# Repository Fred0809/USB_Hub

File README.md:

# USB_Hub

This is a project on USB hub/switch. Two input devices, toggle switch, and up to 4 output devices

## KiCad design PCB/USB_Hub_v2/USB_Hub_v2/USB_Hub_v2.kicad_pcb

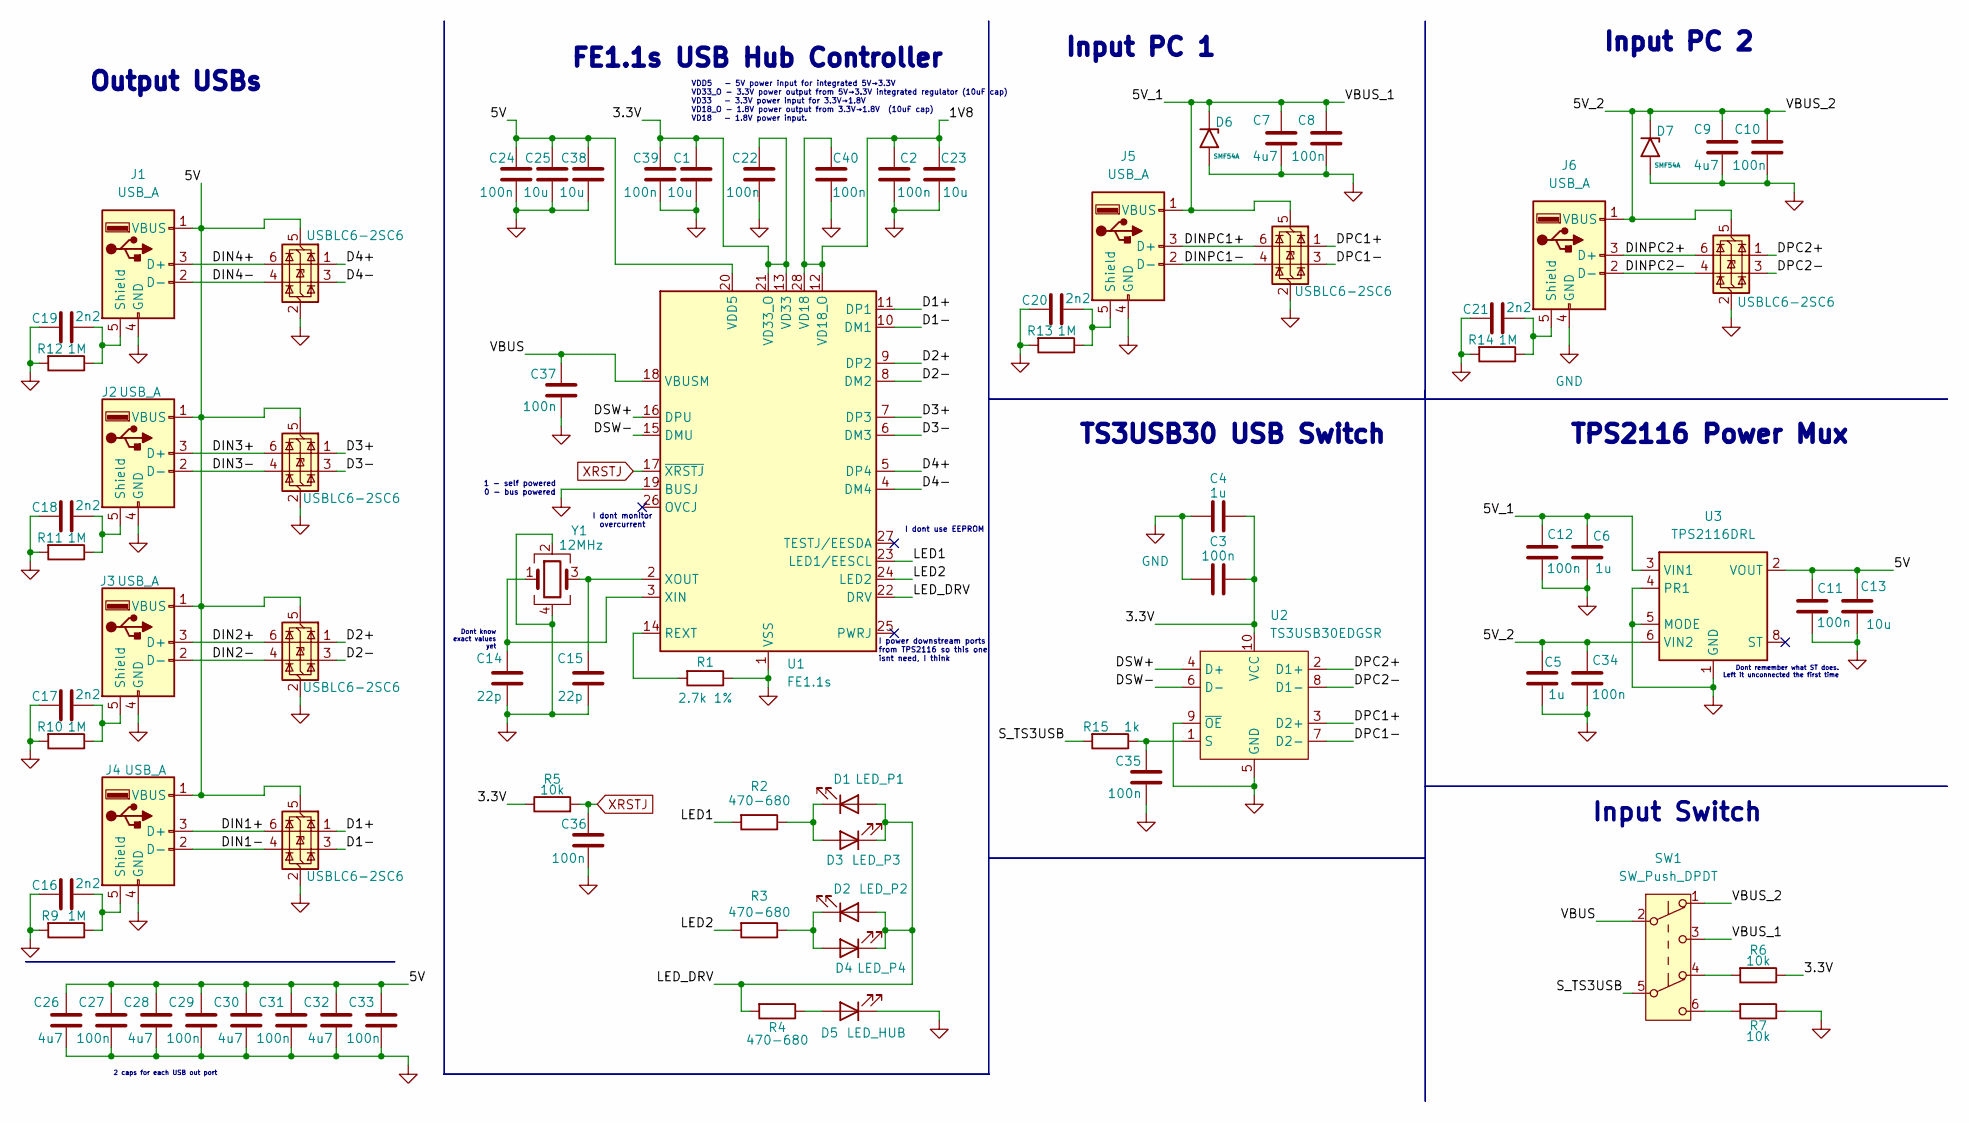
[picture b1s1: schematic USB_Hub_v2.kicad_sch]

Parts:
C1, C13, C23, C25, C38: 10u; C_0805_2012Metric_Pad1.18x1.45mm_HandSolder
C2, C3, C8, C10, C11, C12, C22, C24, C27, C29, C31, C33, C34, C35, C36, C37, C39, C40: 100n; C_0805_2012Metric_Pad1.18x1.45mm_HandSolder
C4, C5, C6: 1u; C_0805_2012Metric_Pad1.18x1.45mm_HandSolder
C7, C9, C26, C28, C30, C32: 4u7; C_0805_2012Metric_Pad1.18x1.45mm_HandSolder
C14, C15: 22p; C_0805_2012Metric_Pad1.18x1.45mm_HandSolder
C16, C17, C18, C19, C20, C21: 2n2; C_0805_2012Metric_Pad1.18x1.45mm_HandSolder
D1: LED_P1; LED_0805_2012Metric_Pad1.15x1.40mm_HandSolder
D2: LED_P2; LED_0805_2012Metric_Pad1.15x1.40mm_HandSolder
D3: LED_P3; LED_0805_2012Metric_Pad1.15x1.40mm_HandSolder
D4: LED_P4; LED_0805_2012Metric_Pad1.15x1.40mm_HandSolder
D5: LED_HUB; LED_0805_2012Metric_Pad1.15x1.40mm_HandSolder
D6, D7: SMF54A; D_SMF
J1, J2, J3, J4, J5, J6: USB_A; USB_A_Molex_67643_Horizontal
R1: 2.7k 1%; R_0603_1608Metric_Pad0.98x0.95mm_HandSolder
R2, R3, R4: 470-680; R_0603_1608Metric_Pad0.98x0.95mm_HandSolder
R5, R6, R7: 10k; R_0603_1608Metric_Pad0.98x0.95mm_HandSolder
R9, R10, R11, R12, R13, R14: 1M; R_0603_1608Metric_Pad0.98x0.95mm_HandSolder
R15: 1k; R_0603_1608Metric_Pad0.98x0.95mm_HandSolder
SW1: SW_Push_DPDT; SW_NKK_G1xJP
U1: FE1.1s; SSOP-28_3.9x9.9mm_P0.635mm
U2: TS3USB30EDGSR; VSSOP-10_3x3mm_P0.5mm
U3: TPS2116DRL; SOT-583-8
U4, U5, U6, U7, U8, U9: USBLC6-2SC6; SOT-23-6
Y1: 12MHz; Crystal_SMD_3225-4Pin_3.2x2.5mm

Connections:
/1V8: C2.2, C23.2, C40.2, U1.12 (VD18_O), U1.28 (VD18)
/3.3V: C1.2, C3.2, C4.2, C22.2, C39.2, R5.1, R6.1, U1.13 (VD33), U1.21 (VD33_O), U2.10 (VCC)
/5V: C11.1, C13.2, C24.2, C25.2, C26.2, C27.2, C28.2, C29.2, C30.2, C31.2, C32.2, C33.2, C38.2, J1.1 (VBUS), J2.1 (VBUS), J3.1 (VBUS), J4.1 (VBUS), U1.20 (VDD5), U3.2 (VOUT), U3.7 (VOUT), U4.5 (VBUS), U5.5 (VBUS), U6.5 (VBUS), U7.5 (VBUS)
/5V_1: C6.2, C7.2, C8.2, C12.1, D6.1 (A1), J5.1 (VBUS), SW1.3 (C), U3.3 (VIN1), U8.5 (VBUS)
/5V_2: C5.2, C9.2, C10.2, C34.1, D7.1 (A1), J6.1 (VBUS), SW1.1 (A), U3.6 (VIN2), U9.5 (VBUS)
/D1+: U1.11 (DP1), U7.1 (I/O1)
/D1-: U1.10 (DM1), U7.3 (I/O2)
/D2+: U1.9 (DP2), U6.1 (I/O1)
/D2-: U1.8 (DM2), U6.3 (I/O2)
/D3+: U1.7 (DP3), U5.1 (I/O1)
/D3-: U1.6 (DM3), U5.3 (I/O2)
/D4+: U1.5 (DP4), U4.1 (I/O1)
/D4-: U1.4 (DM4), U4.3 (I/O2)
/DIN1+: J4.3 (D+), U7.6 (I/O1)
/DIN1-: J4.2 (D-), U7.4 (I/O2)
/DIN2+: J3.3 (D+), U6.6 (I/O1)
/DIN2-: J3.2 (D-), U6.4 (I/O2)
/DIN3+: J2.3 (D+), U5.6 (I/O1)
/DIN3-: J2.2 (D-), U5.4 (I/O2)
/DIN4+: J1.3 (D+), U4.6 (I/O1)
/DIN4-: J1.2 (D-), U4.4 (I/O2)
/DINPC1+: J5.3 (D+), U8.6 (I/O1)
/DINPC1-: J5.2 (D-), U8.4 (I/O2)
/DINPC2+: J6.3 (D+), U9.6 (I/O1)
/DINPC2-: J6.2 (D-), U9.4 (I/O2)
/DPC1+: U2.3 (D2+), U8.1 (I/O1)
/DPC1-: U2.7 (D2-), U8.3 (I/O2)
/DPC2+: U2.2 (D1+), U9.1 (I/O1)
/DPC2-: U2.8 (D1-), U9.3 (I/O2)
/DSW+: U1.16 (DPU), U2.4 (D+)
/DSW-: U1.15 (DMU), U2.6 (D-)
/LED1: R2.2, U1.23 (LED1/EESCL)
/LED2: R3.2, U1.24 (LED2)
/LED_DRV: D1.2 (A), D2.2 (A), D3.1 (K), D4.1 (K), R4.2, U1.22 (DRV)
/S_TS3USB: R15.2, SW1.5 (B)
/VBUS: C37.2, SW1.2 (B), U1.18 (VBUSM)
GND: C1.1, C2.1, C3.1, C4.1, C5.1, C6.1, C7.1, C8.1, C9.1, C10.1, C11.2, C12.2, C13.1, C14.1, C15.1, C16.1, C17.1, C18.1, C19.1, C20.1, C21.1, C22.1, C23.1, C24.1, C25.1, C26.1, C27.1, C28.1, C29.1, C30.1, C31.1, C32.1, C33.1, C34.2, C35.1, C36.1, C37.1, C38.1, C39.1, C40.1, D5.1 (K), D6.2 (A2), D7.2 (A2), J1.4 (GND), J2.4 (GND), J3.4 (GND), J4.4 (GND), J5.4 (GND), J6.4 (GND), R1.1, R7.1, R9.2, R10.2, R11.2, R12.2, R13.2, R14.2, U1.1 (VSS), U1.19 (BUSJ), U2.5 (GND), U2.9 (~OE), U3.1 (GND), U3.4 (PR1), U3.5 (MODE), U4.2 (GND), U5.2 (GND), U6.2 (GND), U7.2 (GND), U8.2 (GND), U9.2 (GND), Y1.2, Y1.4
unnamed: D1.1 (K), D3.2 (A), R2.1
unnamed: D2.1 (K), D4.2 (A), R3.1
unnamed: D5.2 (A), R4.1
unnamed: C19.2, J1.5 (Shield), R12.1
unnamed: C18.2, J2.5 (Shield), R11.1
unnamed: C17.2, J3.5 (Shield), R10.1
unnamed: C16.2, J4.5 (Shield), R9.1
unnamed: C20.2, J5.5 (Shield), R13.1
unnamed: C21.2, J6.5 (Shield), R14.1
unnamed: R6.2, SW1.4 (A)
unnamed: R7.2, SW1.6 (C)
unnamed: R1.2, U1.14 (REXT)
unnamed: C14.2, U1.3 (XIN), Y1.1
unnamed: C15.2, U1.2 (XOUT), Y1.3
unnamed: C35.2, R15.1, U2.1 (S)
XRSTJ: C36.2, R5.2, U1.17 (~XRSTJ)

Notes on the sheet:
Input PC 2
TS3USB30 USB Switch
I dont use EEPROM
TPS2116 Power Mux
Input PC 1
FE1.1s USB Hub Controller
Output USBs
VDD5 - 5V power input for integrated 5V→3.3V VD33_O - 3.3V power output from 5V→3.3V integrated regulator (10uF cap) VD33 - 3.3V power input for 3.3V→1.8V VD18_O - 1.8V power output from 3.3V→1.8V (10uF cap) VD18 - 1.8V power input.
Dont remember what ST does. Left it unconnected the first time
1 - self powered 0 - bus powered
2 caps for each USB out port
Input Switch
Dont know exact values yet
I dont monitor overcurrent
I power downstream ports from TPS2116 so this one isnt need, I think

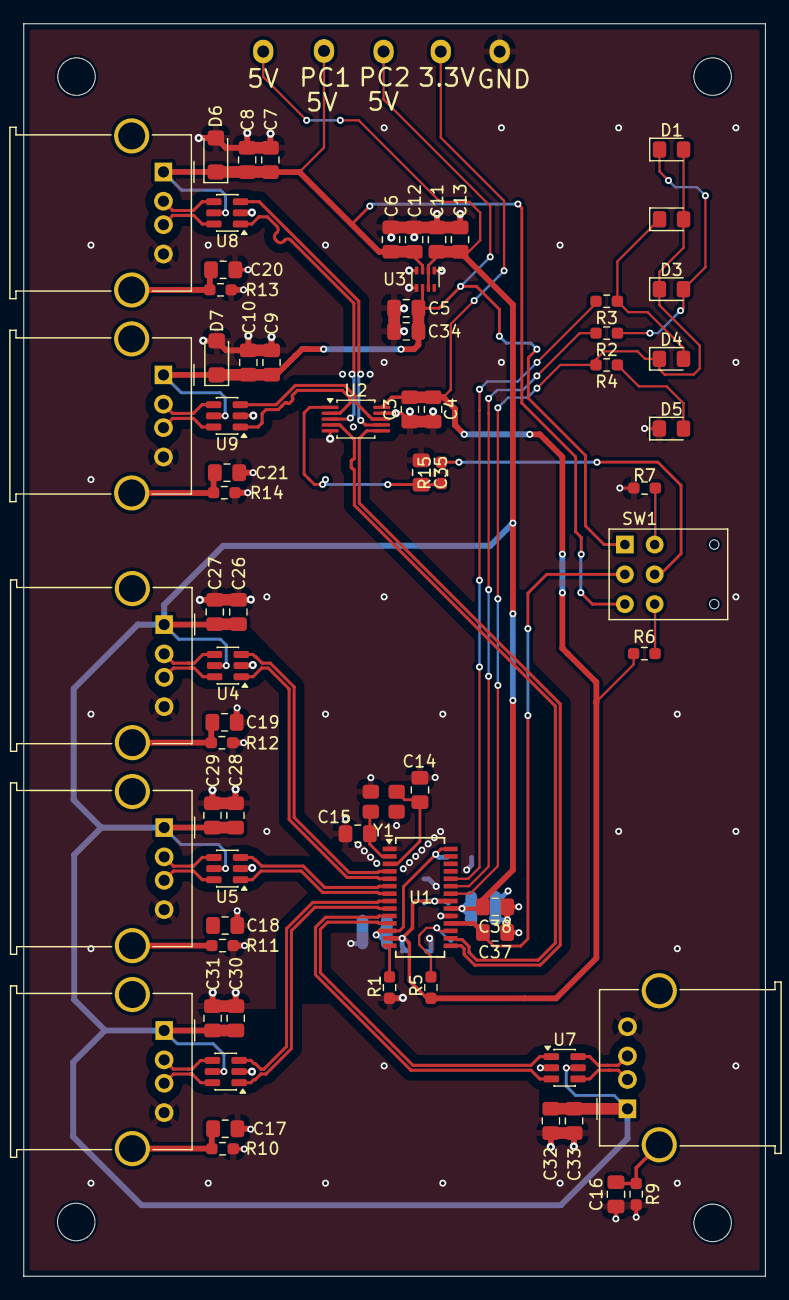
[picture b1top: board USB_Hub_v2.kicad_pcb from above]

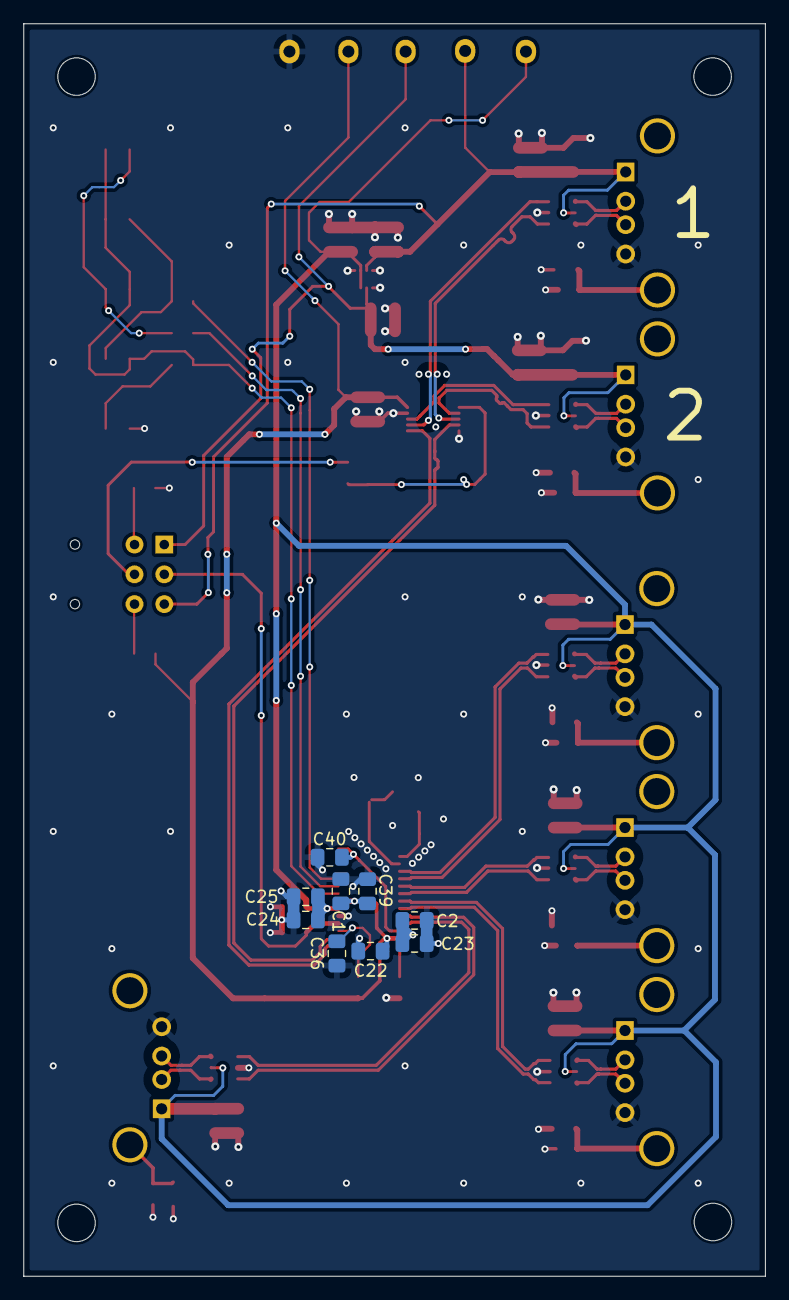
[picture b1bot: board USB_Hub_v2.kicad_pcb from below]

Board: 4 copper layers, 63.2 x 106.8 mm, 78 parts (9 on the bottom side), 53 nets.

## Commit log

2025-12-28 Add PCB images and USB hub schematic
    Added PCB_1.png and PCB_2.png images along with USB_Hub.pdf schematic to the PCB directory for documentation and reference.
2025-12-28 Add case design files and STL exports
    Added FreeCAD project files and corresponding STL exports for multiple case designs, including Case, Case_2, and HUB_Case. These files provide source and printable models for the project's enclosures.
2025-12-28 Add datasheets for FE1.1s, TPS2116, and TS3USB30E
    Added PDF datasheets for the FE1.1s, TPS2116, and TS3USB30E components to the Datasheet directory for reference.
2025-12-29 Add 3D PCB image
    Added pcb_3d.png to the PCB directory to provide a 3D visualization of the PCB layout.
2026-02-01 Add USB Hub Pro PCB design files and 3D models
    Initial commit of USB Hub Pro project files, including KiCad PCB and schematic files, 3D case models (STL and FreeCAD formats), PCB images, Gerber files for manufacturing, and backup archives. This p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
2026-02-01 Add project description for USB hub/switch
2026-02-04 Move USB_Hub_Pro to v1 and add v2 files
    Delete obsolete Pro images and relocate the USB_Hub_Pro project into PCB/USB_Hub_v1 (3D models, KiCad project files, gerbers, backups). Add a new PCB/USB_Hub_v2 folder with KiCad files, fp-info-cache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
2026-02-05 Update PCB layout: stackup, nets and footprints
    Add recent PCB backup archives and apply extensive KiCad PCB updates: define board stackup and layer types (B.Cu -> power), rename/reorder nets, and replace/update multiple footprints and component p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
2026-02-10 Adjust KiCad footprints and add backups
    Rotate/reposition multiple SMD footprints, update pad rotations, fp_line/fp_text orientations and UUIDs in USB_Hub_v2.kicad_pcb (and related project files). Also update USB_Hub_v2.kicad_pro/.kicad_sc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
2026-02-10 Update KiCad PCB footprints, nets & backups
    Enable dielectric constraints and introduce Net-(U2-S) (net 58); correct several pad/net assignments to use Net-(U2-S) instead of the old net, and update many footprint positions, rotations, silk/fab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
2026-02-11 Update PCB layout: reroute nets and add backups
    Add multiple USB_Hub_v2 backup zip snapshots and update KiCad project files. USB_Hub_v2.kicad_pcb: swap DPC1/DPC2 net assignments, hide C9 silkscreen reference, and apply extensive track/via repositi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
2026-02-16 Rev 2 finished
    Updated layout and added parts to improve next version
2026-02-27 Layout update
